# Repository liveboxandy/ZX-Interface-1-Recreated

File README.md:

# ZX-Interface-1-Recreated
Sinclair ZX Interface 1 recreated with the orignal Sinclair Routing

This is Kicad 9 project of the Sinclair ZX Interface 1 that uses the same routing and PCB dimensions as the orignal.
A raw board was scanned and the top and bottom side images were imported into Kicad. This gave the board outline 
along with the position of components and the track layout.
The schematic available from the Service Guide was then redrawn in Kicad and used to recreate the PCB and to verify that the routing was correct.

The Bill of Materials from the Service Guide was used to select suitable footprints. Some parts were obsolete and could not be located and so suitable repalcements were used.

Q11 does not have a place on the Sinclair PCB as it was an afterthought. To stop Kicad moaning I have placed it within the footprint of R2 which is not fitted.

This is the result of that exercise.

The files 'Interface 1 Recreated with images.*' when combined will produce an Interface 1 Recreated.kicad_pcb file that includes the top/bottom images. It appears that a 75MB is too be for uploading so I split it into 20MB chunks.

Sometimes Kicad complains that there is an issue with the edge.cuts file. Running DRC will show what it doesn't like and it's easy to fix so that the board outline is a closed shape.

The bom/ibom.html is an interactive BOM that will show component position as well as routing in a web browser.

Have fun.

Comments - Good Bad or totally indifferent on https://www.facebook.com/groups/zxspa/

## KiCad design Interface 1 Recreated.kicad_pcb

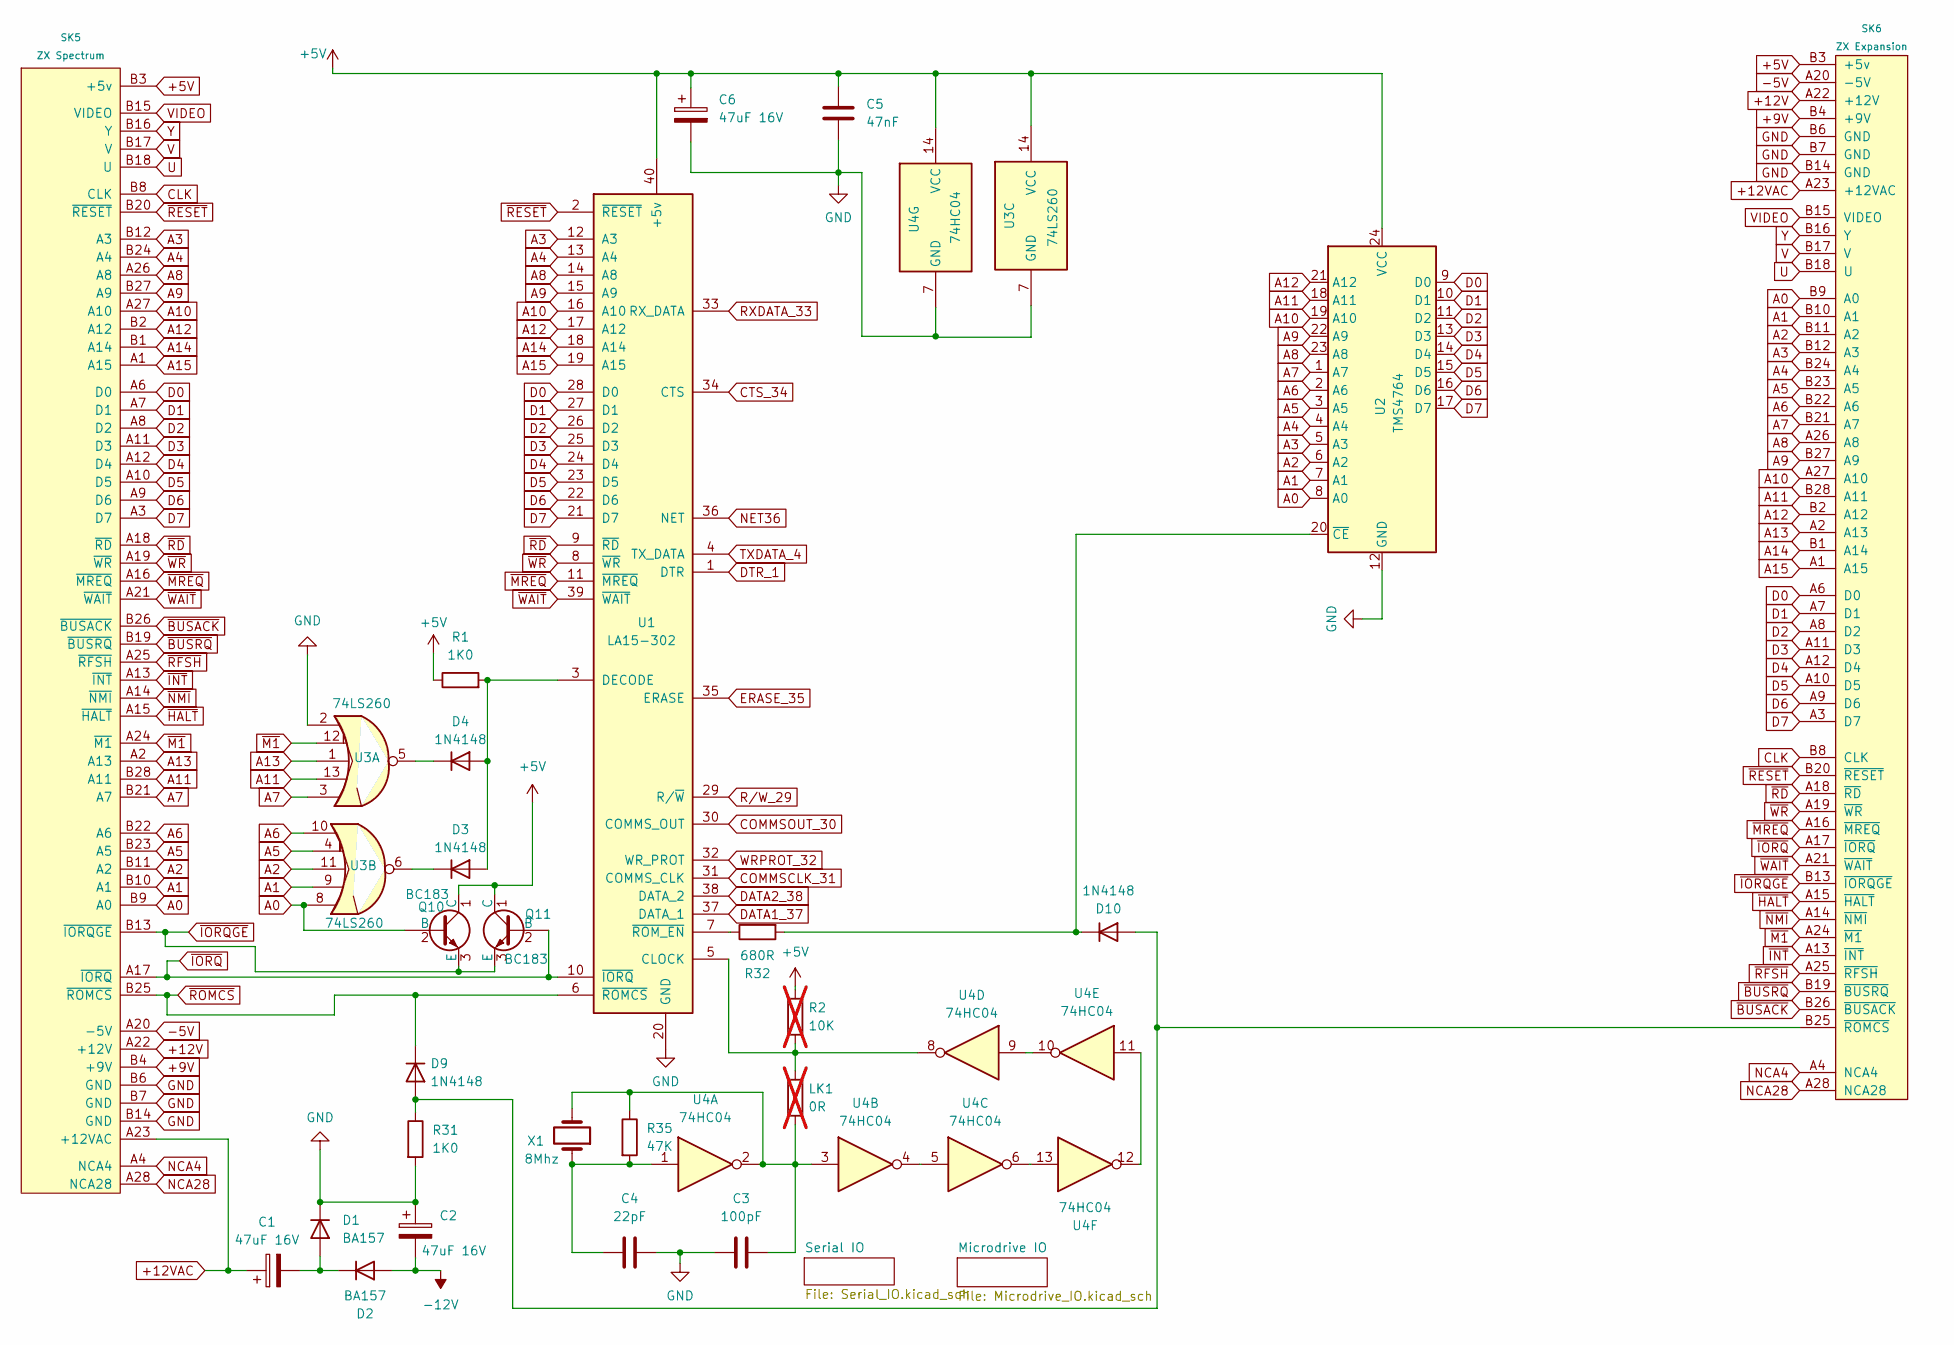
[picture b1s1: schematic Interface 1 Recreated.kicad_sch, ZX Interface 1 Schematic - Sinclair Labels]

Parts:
C1, C2, C6: 47uF 16V; C_Axial_L17.0mm_D6.5mm_P20.00mm_Horizontal
C3: 100pF; Capacitor Ceramic
C4: 22pF; Capacitor Ceramic
C5: 47nF; C_Axial_L3.8mm_D2.6mm_P12.50mm_Horizontal
D1, D2: BA157; Diode 1N
D3, D4, D9, D10: 1N4148; Diode 1N
LK1: 0R; Resistor_0.25W; not fitted
Q10, Q11: BC183; TO-92L_Inline_Wide
R1, R31: 1K0; Resistor_0.25W
R2: 10K; Resistor_0.25W; not fitted
R32: 680R; Resistor_0.25W
R35: 47K; Resistor_0.25W
SK5: ZX Spectrum; Edge_Connector_Up_To_Spectrum
SK6: ZX Expansion; Edge_Connector_To_AddOn
U1: LA15-302; DIP-40_W15.24mm
U2: TMS4764; DIP-24_W15.24mm
U3: 74LS260; DIP-14_W7.62mm
U4: 74HC04; DIP-14_W7.62mm
X1: 8Mhz; Crystal_HC18-U_Horizontal

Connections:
+5V: C5.1, C6.1, Q10.1 (C), Q11.1 (C), R1.1, R2.1, SK5.B3 (+5v), SK6.B3 (+5v), U1.40 (+5v), U2.24 (VCC), U3.14 (VCC), U4.14 (VCC); also elsewhere on the board
+9V: SK5.B4 (+9V), SK6.B4 (+9V); also elsewhere on the board
+12V: SK5.A22 (+12V), SK6.A22 (+12V); also elsewhere on the board
+12VAC: C1.1, SK5.A23 (+12VAC), SK6.A23 (+12VAC)
-5V: SK5.A20 (-5V), SK6.A20 (-5V)
-12V: C2.2, D2.2 (A); also elsewhere on the board
A0: Q10.2 (B), SK5.B9 (A0), SK6.B9 (A0), U2.8 (A0), U3.8
A1: SK5.B10 (A1), SK6.B10 (A1), U2.7 (A1), U3.9
A2: SK5.B11 (A2), SK6.B11 (A2), U2.6 (A2), U3.11
A3: SK5.B12 (A3), SK6.B12 (A3), U1.12 (A3), U2.5 (A3)
A4: SK5.B24 (A4), SK6.B24 (A4), U1.13 (A4), U2.4 (A4)
A5: SK5.B23 (A5), SK6.B23 (A5), U2.3 (A5), U3.4
A6: SK5.B22 (A6), SK6.B22 (A6), U2.2 (A6), U3.10
A7: SK5.B21 (A7), SK6.B21 (A7), U2.1 (A7), U3.3
A8: SK5.A26 (A8), SK6.A26 (A8), U1.14 (A8), U2.23 (A8)
A9: SK5.B27 (A9), SK6.B27 (A9), U1.15 (A9), U2.22 (A9)
A10: SK5.A27 (A10), SK6.A27 (A10), U1.16 (A10), U2.19 (A10)
A11: SK5.B28 (A11), SK6.B28 (A11), U2.18 (A11), U3.13
A12: SK5.B2 (A12), SK6.B2 (A12), U1.17 (A12), U2.21 (A12)
A13: SK5.A2 (A13), SK6.A2 (A13), U3.1
A14: SK5.B1 (A14), SK6.B1 (A14), U1.18 (A14)
A15: SK5.A1 (A15), SK6.A1 (A15), U1.19 (A15)
CLK: SK5.B8 (CLK), SK6.B8 (CLK)
COMMSCLK_31: U1.31 (COMMS_CLK); also elsewhere on the board
COMMSOUT_30: U1.30 (COMMS_OUT); also elsewhere on the board
CTS_34: U1.34 (CTS); also elsewhere on the board
D0: SK5.A6 (D0), SK6.A6 (D0), U1.28 (D0), U2.9 (D0)
D1: SK5.A7 (D1), SK6.A7 (D1), U1.27 (D1), U2.10 (D1)
D2: SK5.A8 (D2), SK6.A8 (D2), U1.26 (D2), U2.11 (D2)
D3: SK5.A11 (D3), SK6.A11 (D3), U1.25 (D3), U2.13 (D3)
D4: SK5.A12 (D4), SK6.A12 (D4), U1.24 (D4), U2.14 (D4)
D5: SK5.A10 (D5), SK6.A10 (D5), U1.23 (D5), U2.15 (D5)
D6: SK5.A9 (D6), SK6.A9 (D6), U1.22 (D6), U2.16 (D6)
D7: SK5.A3 (D7), SK6.A3 (D7), U1.21 (D7), U2.17 (D7)
DATA1_37: U1.37 (DATA_1); also elsewhere on the board
DATA2_38: U1.38 (DATA_2); also elsewhere on the board
DTR_1: U1.1 (DTR); also elsewhere on the board
ERASE_35: U1.35 (ERASE); also elsewhere on the board
GND: C2.1, C3.2, C4.1, C5.2, C6.2, D1.1 (K), R31.2, SK5.B6 (GND), SK5.B7 (GND), SK5.B14 (GND), SK6.B6 (GND), SK6.B7 (GND), SK6.B14 (GND), U1.20 (GND), U2.12 (GND), U3.2, U3.7 (GND), U4.7 (GND); also elsewhere on the board
NCA4: SK5.A4 (NCA4), SK6.A4 (NCA4)
NCA28: SK5.A28 (NCA28), SK6.A28 (NCA28)
NET36: U1.36 (NET); also elsewhere on the board
unnamed: C3.1, LK1.2, R35.1, U4.2, U4.3, X1.2
unnamed: C4.2, R35.2, U4.1, X1.1
unnamed: C1.2, D1.2 (A), D2.1 (K)
unnamed: D3.2 (A), D4.2 (A), R1.2, U1.3 (DECODE)
unnamed: D3.1 (K), U3.6
unnamed: D4.1 (K), U3.5
unnamed: D9.2 (A), D10.2 (A), R31.1, SK6.B25 (~ROMCS)
unnamed: D10.1 (K), R32.2, U2.20 (~CE)
unnamed: LK1.1, R2.2, U1.5 (CLOCK), U4.8
unnamed: R32.1, U1.7 (~ROM_EN)
unnamed: U4.4, U4.5
unnamed: U4.9, U4.10
unnamed: U4.11, U4.12
unnamed: U4.6, U4.13
RXDATA_33: U1.33 (RX_DATA); also elsewhere on the board
R/W_29: U1.29 (R/~W); also elsewhere on the board
TXDATA_4: U1.4 (TX_DATA); also elsewhere on the board
U: SK5.B18 (U), SK6.B18 (U)
V: SK5.B17 (V), SK6.B17 (V)
VIDEO: SK5.B15 (VIDEO), SK6.B15 (VIDEO)
WRPROT_32: U1.32 (WR_PROT); also elsewhere on the board
Y: SK5.B16 (Y), SK6.B16 (Y)
~BUSACK: SK5.B26 (~BUSACK), SK6.B26 (~BUSACK)
~BUSRQ: SK5.B19 (~BUSRQ), SK6.B19 (~BUSRQ)
~HALT: SK5.A15 (~HALT), SK6.A15 (~HALT)
~INT: SK5.A13 (~INT), SK6.A13 (~INT)
~IORQGE: Q10.3 (E), Q11.3 (E), SK5.B13 (~IORQGE), SK6.B13 (~IORQGE)
~IORQ: Q11.2 (B), SK5.A17 (~IORQ), SK6.A17 (~IORQ), U1.10 (~IORQ)
~M1: SK5.A24 (~M1), SK6.A24 (~M1), U3.12
~MREQ: SK5.A16 (~MREQ), SK6.A16 (~MREQ), U1.11 (~MREQ)
~NMI: SK5.A14 (~NMI), SK6.A14 (~NMI)
~RD: SK5.A18 (~RD), SK6.A18 (~RD), U1.9 (~RD)
~RESET: SK5.B20 (~RESET), SK6.B20 (~RESET), U1.2 (~RESET)
~RFSH: SK5.A25 (~RFSH), SK6.A25 (~RFSH)
~ROMCS: D9.1 (K), SK5.B25 (~ROMCS), U1.6 (~ROMCS)
~WAIT: SK5.A21 (~WAIT), SK6.A21 (~WAIT), U1.39 (~WAIT)
~WR: SK5.A19 (~WR), SK6.A19 (~WR), U1.8 (~WR)

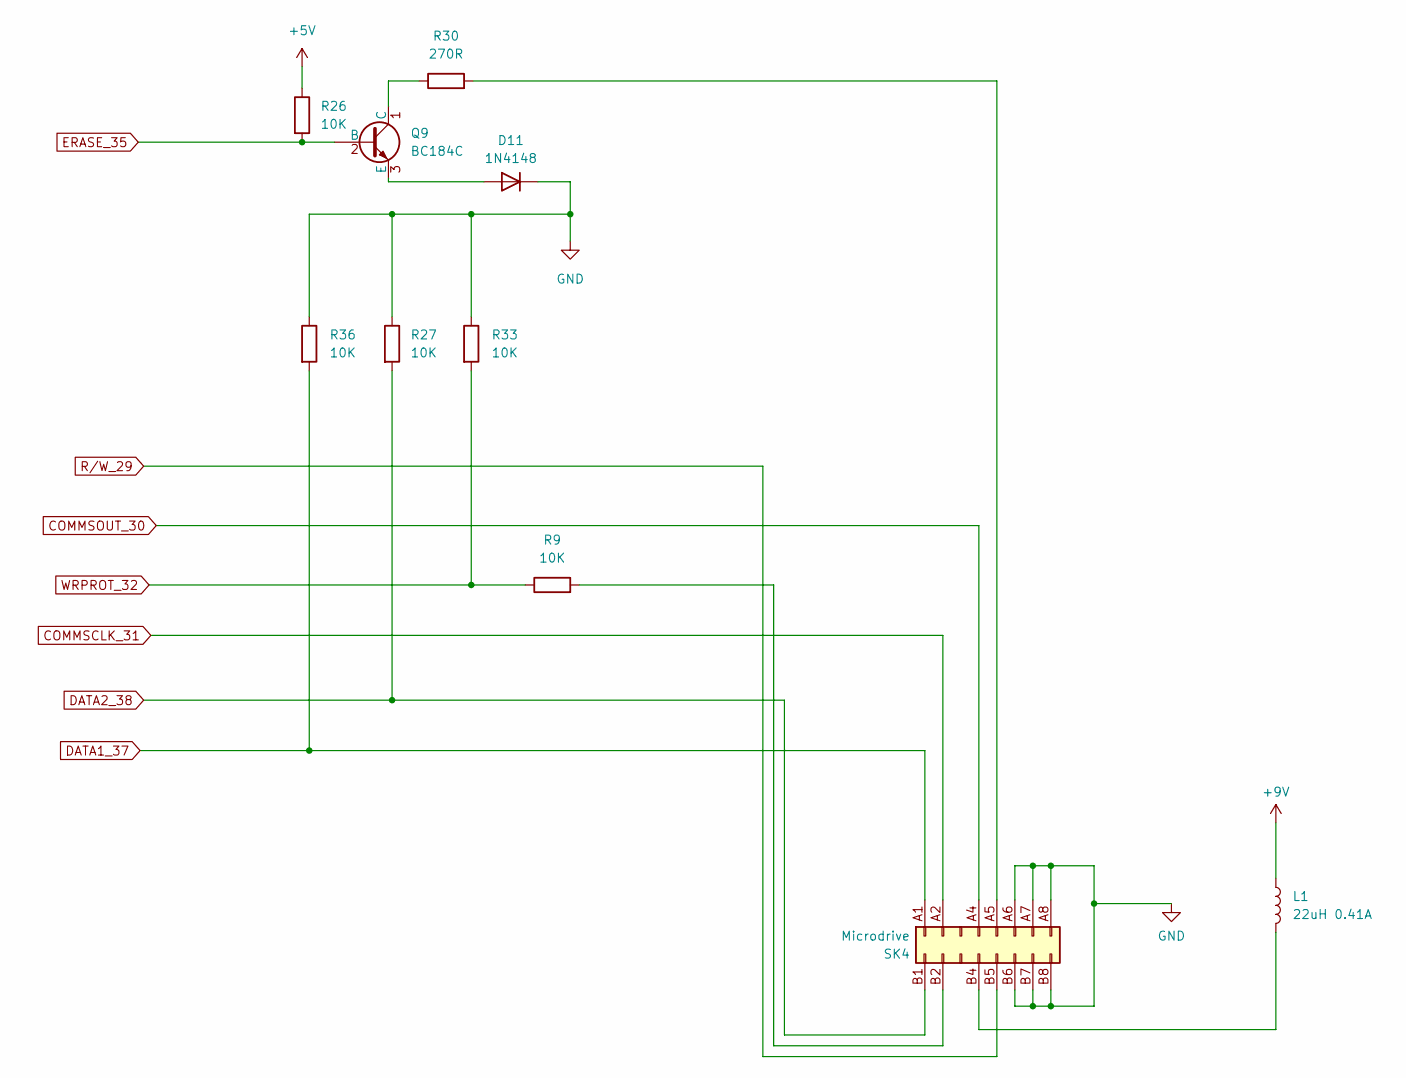
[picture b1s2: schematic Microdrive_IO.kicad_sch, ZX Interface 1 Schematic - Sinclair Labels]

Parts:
D11: 1N4148; Diode 1N
L1: 22uH 0.41A; L_Axial_L12.8mm_D5.8mm_P20.32mm_Horizontal_Fastron_HBCC
Q9: BC184C; TO-92L_Inline_Wide
R9, R26, R27, R33, R36: 10K; Resistor_0.25W
R30: 270R; Resistor_0.25W
SK4: Microdrive; ZX_MD_Edge_Connector

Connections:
+5V: R26.1; also elsewhere on the board
+9V: L1.1; also elsewhere on the board
COMMSCLK_31: SK4.A2; also elsewhere on the board
COMMSOUT_30: SK4.A4; also elsewhere on the board
DATA1_37: R36.2, SK4.A1; also elsewhere on the board
DATA2_38: R27.2, SK4.B1; also elsewhere on the board
ERASE_35: Q9.2 (B), R26.2; also elsewhere on the board
GND: D11.1 (K), R27.1, R33.1, R36.1, SK4.A6, SK4.A7, SK4.A8, SK4.B6, SK4.B7, SK4.B8; also elsewhere on the board
unnamed: D11.2 (A), Q9.3 (E)
unnamed: Q9.1 (C), R30.1
unnamed: R30.2, SK4.A5
unnamed: R9.2, SK4.B2
unnamed: L1.2, SK4.B4
R/W_29: SK4.B5; also elsewhere on the board
WRPROT_32: R9.1, R33.2; also elsewhere on the board

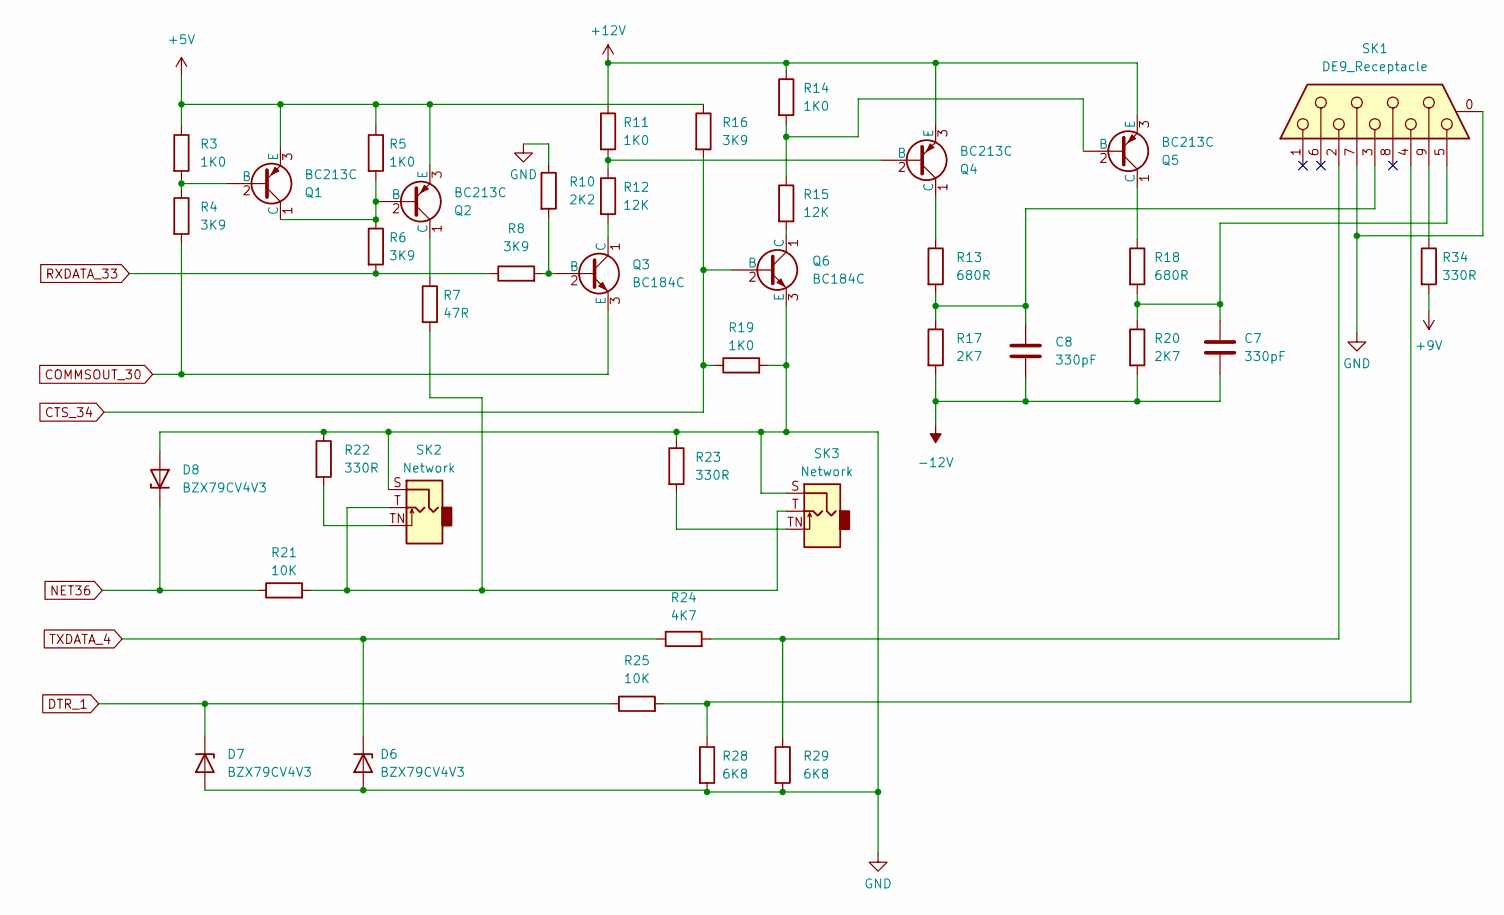
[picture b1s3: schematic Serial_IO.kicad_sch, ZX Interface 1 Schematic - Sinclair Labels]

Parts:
C7, C8: 330pF; Capacitor Ceramic
D6, D7, D8: BZX79CV4V3; Diode 1N
Q1, Q2, Q4, Q5: BC213C; TO-92L_Inline_Wide
Q3, Q6: BC184C; TO-92L_Inline_Wide
R3, R5, R11, R14, R19: 1K0; Resistor_0.25W
R4, R6, R8, R16: 3K9; Resistor_0.25W
R7: 47R; Resistor_0.25W
R10: 2K2; Resistor_0.25W
R12, R15: 12K; Resistor_0.25W
R13, R18: 680R; Resistor_0.25W
R17, R20: 2K7; Resistor_0.25W
R21, R25: 10K; Resistor_0.25W
R22, R23, R34: 330R; Resistor_0.25W
R24: 4K7; Resistor_0.25W
R28, R29: 6K8; Resistor_0.25W
SK1: DE9_Receptacle; DSUB-9_Female_Horizontal_P2.77x2.84mm_EdgePinOffset14.56mm_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
SK2, SK3: Network; ZX Spectrum 3.5mm Skt

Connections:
+5V: Q1.3 (E), Q2.3 (E), R3.1, R5.1, R16.1; also elsewhere on the board
+9V: R34.2; also elsewhere on the board
+12V: Q4.3 (E), Q5.3 (E), R11.1, R14.1; also elsewhere on the board
-12V: C7.2, C8.2, R17.2, R20.2; also elsewhere on the board
COMMSOUT_30: Q3.3 (E), R4.2; also elsewhere on the board
CTS_34: Q6.2 (B), R16.2, R19.1; also elsewhere on the board
DTR_1: D7.1 (K), R25.1; also elsewhere on the board
GND: D6.2 (A), D7.2 (A), D8.2 (A), Q6.3 (E), R10.1, R19.2, R22.1, R23.1, R28.2, R29.2, SK1.0 (PAD), SK1.7, SK2.S, SK3.S; also elsewhere on the board
NET36: D8.1 (K), R21.1; also elsewhere on the board
unnamed: C7.1, R18.2, R20.1, SK1.5
unnamed: C8.1, R13.2, R17.1, SK1.3
unnamed: Q1.2 (B), R3.2, R4.1
unnamed: Q1.1 (C), Q2.2 (B), R5.2, R6.1
unnamed: Q2.1 (C), R7.1
unnamed: Q3.2 (B), R8.2, R10.2
unnamed: Q3.1 (C), R12.2
unnamed: Q4.2 (B), R11.2, R12.1
unnamed: Q4.1 (C), R13.1
unnamed: Q5.2 (B), R14.2, R15.1
unnamed: Q5.1 (C), R18.1
unnamed: Q6.1 (C), R15.2
unnamed: R7.2, R21.2, SK2.T, SK3.T
unnamed: R22.2, SK2.TN
unnamed: R23.2, SK3.TN
unnamed: R24.2, R29.1, SK1.2
unnamed: R25.2, R28.1, SK1.4
unnamed: R34.1, SK1.9
RXDATA_33: R6.2, R8.1; also elsewhere on the board
TXDATA_4: D6.1 (K), R24.1; also elsewhere on the board

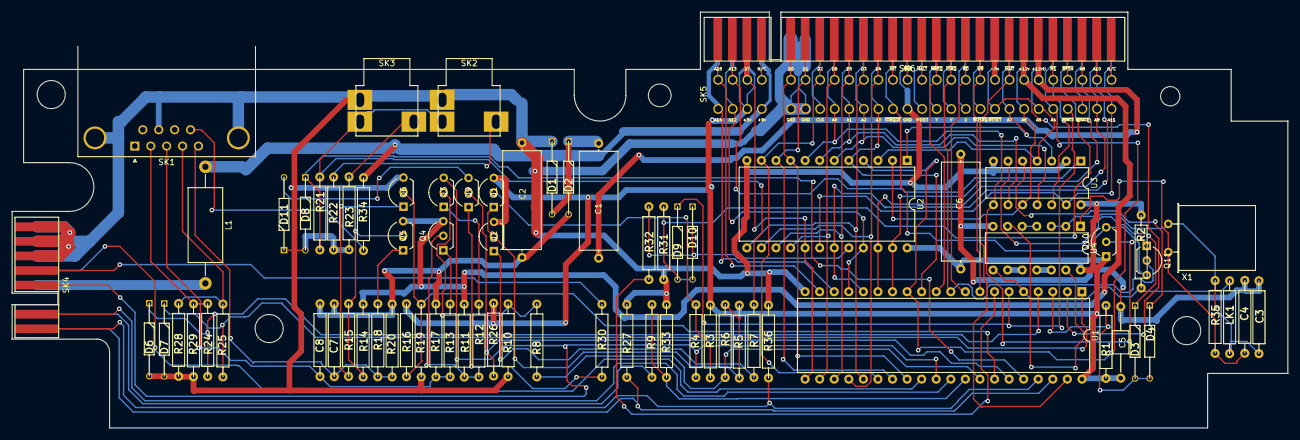
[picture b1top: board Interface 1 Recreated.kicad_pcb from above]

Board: 2 copper layers, 222.4 x 72.5 mm, 76 parts (0 on the bottom side), 102 nets.

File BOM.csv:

"Reference","Value","Datasheet","Footprint","Qty","DNP"
"C1,C2,C6","47uF 16V","~","Capacitor_THT:C_Axial_L17.0mm_D6.5mm_P20.00mm_Horizontal","3",""
"C3","100pF","~","Spectrum:Capacitor Ceramic","1",""
"C4","22pF","~","Spectrum:Capacitor Ceramic","1",""
"C5","47nF","~","Capacitor_THT:C_Axial_L3.8mm_D2.6mm_P12.50mm_Horizontal","1",""
"C7,C8","330pF","~","Spectrum:Capacitor Ceramic","2",""
"D1,D2","BA157","https://www.vishay.com/docs/88536/ba157.pdf","Spectrum:Diode 1N","2",""
"D3,D4,D9,D10,D11","1N4148","https://assets.nexperia.com/documents/data-sheet/1N4148_1N4448.pdf","Spectrum:Diode 1N","5",""
"D6,D7,D8","BZX79CV4V3","~","Spectrum:Diode 1N","3",""
"L1","22uH 0.41A","~","Inductor_THT:L_Axial_L12.8mm_D5.8mm_P20.32mm_Horizontal_Fastron_HBCC","1",""
"NoFit1","0R","~","Spectrum:Resistor_0.25W","1","DNP"
"Q1,Q2,Q4,Q5","BC213C","~","Package_TO_SOT_THT:TO-92L_Inline_Wide","4",""
"Q3,Q6,Q9","BC184C","~","Package_TO_SOT_THT:TO-92L_Inline_Wide","3",""
"Q10,Q11","BC183","~","Package_TO_SOT_THT:TO-92L_Inline_Wide","2",""
"R1,R3,R5,R11,R14,R19,R31","1K0","-- mixed values --","-- mixed values --","7",""
"R2","NoFit","~","Spectrum:Resistor_0.25W","1","DNP"
"R4,R6,R8,R16","3K9","~","Spectrum:Resistor_0.25W","4",""
"R7","47R","~","Spectrum:Resistor_0.25W","1",""
"R9,R21,R25,R26,R27,R33,R36","10K","~","Spectrum:Resistor_0.25W","7",""
"R10","2K2","~","Spectrum:Resistor_0.25W","1",""
"R12,R15","12K","~","Spectrum:Resistor_0.25W","2",""
"R13,R18,R32","680R","~","Spectrum:Resistor_0.25W","3",""
"R17,R20","2K7","~","Spectrum:Resistor_0.25W","2",""
"R22,R23,R34","330R","~","Spectrum:Resistor_0.25W","3",""
"R24","4K7","~","Spectrum:Resistor_0.25W","1",""
"R28,R29","6K8","~","Spectrum:Resistor_0.25W","2",""
"R30","270R","~","Spectrum:Resistor_0.25W","1",""
"R35","47K","~","Spectrum:Resistor_0.25W","1",""
"SK1","DE9_Receptacle"," ~","Connector_Dsub:DSUB-9_Female_Horizontal_P2.77x2.84mm_EdgePinOffset14.56mm_Housed_MountingHolesOffset15.98mm","1",""
"SK2,SK3","Network","~","ZX Spectrum 3.5mm:ZX Spectrum 3.5mm Skt","2",""
"SK4","Microdrive","~","ZX Bits:ZX_MD_Edge_Connector","1",""
"SK5","ZX Spectrum","","ZX Bits:Spectrum_Edge_Connector","1",""
"SK6","ZX Expansion","","ZX Bits:ZX_Bus_Edge_Connector","1",""
"U1","LA15-302","LA 15-302 Custom ULA","Package_DIP:DIP-40_W15.24mm","1",""
"U2","TMS4764","","Package_DIP:DIP-24_W15.24mm","1",""
"U3","74LS260","","Package_DIP:DIP-14_W7.62mm","1",""
"U4","74HC04","https://assets.nexperia.com/documents/data-sheet/74HC_HCT04.pdf","Package_DIP:DIP-14_W7.62mm","1",""
"X1","8Mhz","~","Crystal:Crystal_HC18-U_Horizontal","1",""

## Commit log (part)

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2023-11-28 Initial README.md
2025-03-06 Update LICENSE
2025-10-22 Add files via upload
    Updated with Kicad 9. Now includes bom/ibom.html (Interactice BOM)
2025-10-22 Add files via upload
    kicad.pcb with images of original PCB Part 1
2025-10-22 Add files via upload
    kicad.pcb with images of original PCB Part 2
2025-10-22 Add files via upload
    kicad.pcb with images of original PCB Part 3
2025-10-22 Add files via upload
    kicad.pcb with images of original PCB Part 4
2025-10-22 Update README.md
    Updated README.md
